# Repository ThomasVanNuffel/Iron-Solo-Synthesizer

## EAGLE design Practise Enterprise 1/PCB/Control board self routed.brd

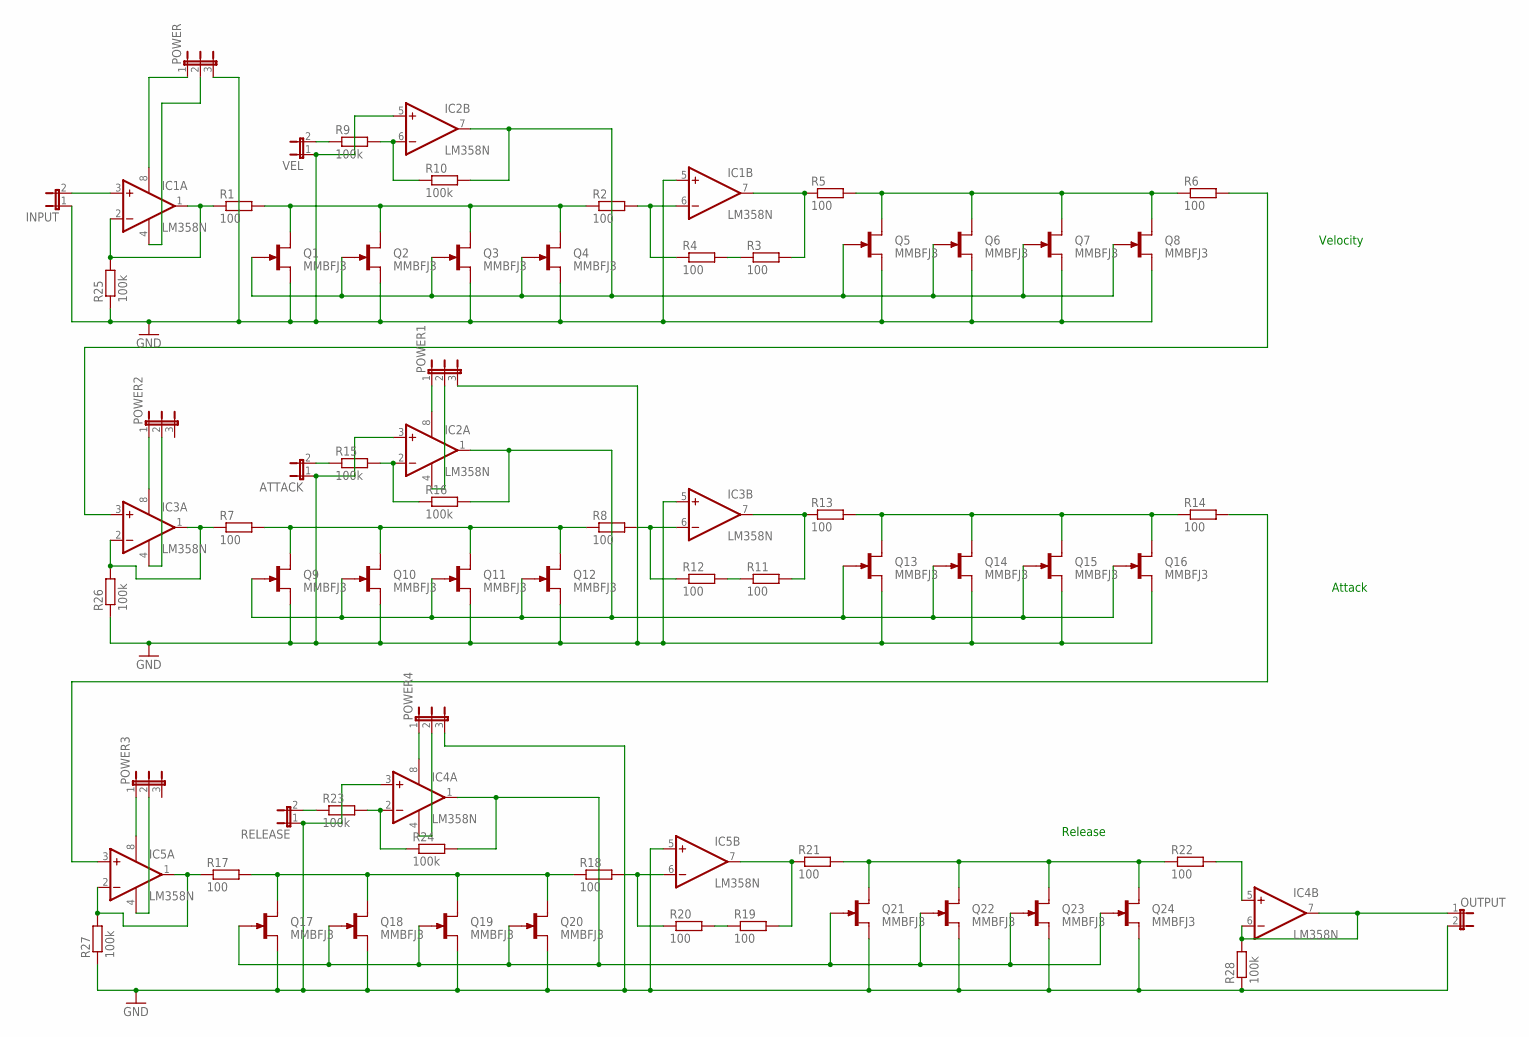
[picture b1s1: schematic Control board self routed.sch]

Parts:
ATTACK: JP1E; JP1
IC1, IC2, IC3, IC4, IC5: LM358N; DIL08
INPUT: JP1E; JP1
OUTPUT: JP1E; JP1
POWER, POWER1, POWER2, POWER3, POWER4: JP2E; JP2
Q1, Q2, Q3, Q4, Q5, Q6, Q7, Q8, Q9, Q10, Q11, Q12, Q13, Q14, Q15, Q16, Q17, Q18, Q19, Q20, Q21, Q22, Q23, Q24: MMBFJ3; SOT23
R1, R2, R3, R4, R5, R6, R7, R8, R11, R12, R13, R14, R17, R18, R19, R20, R21, R22: 100; 0204/7
R9, R10, R15, R16, R23, R24, R25, R26, R27, R28: 100k; 0204/7
RELEASE: JP1E; JP1
VEL: JP1E; JP1

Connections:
22: Q13.1 (D), Q14.1 (D), Q15.1 (D), Q16.1 (D), R13.2, R14.1
CONTROL: IC2.7 (OUT), Q1.3 (G), Q2.3 (G), Q3.3 (G), Q4.3 (G), Q5.3 (G), Q6.3 (G), Q7.3 (G), Q8.3 (G), R10.2
CONTROL1: IC2.1 (OUT), Q9.3 (G), Q10.3 (G), Q11.3 (G), Q12.3 (G), Q13.3 (G), Q14.3 (G), Q15.3 (G), Q16.3 (G), R16.2
CONTROL2: IC4.1 (OUT), Q17.3 (G), Q18.3 (G), Q19.3 (G), Q20.3 (G), Q21.3 (G), Q22.3 (G), Q23.3 (G), Q24.3 (G), R24.2
GND: ATTACK.1, IC1.5 (+IN), IC2.3 (+IN), IC2.5 (+IN), IC3.5 (+IN), IC4.3 (+IN), IC5.5 (+IN), INPUT.1, OUTPUT.2, POWER.3, POWER1.3, POWER4.3, Q1.2 (S), Q2.2 (S), Q3.2 (S), Q4.2 (S), Q5.2 (S), Q6.2 (S), Q7.2 (S), Q8.2 (S), Q9.2 (S), Q10.2 (S), Q11.2 (S), Q12.2 (S), Q13.2 (S), Q14.2 (S), Q15.2 (S), Q16.2 (S), Q17.2 (S), Q18.2 (S), Q19.2 (S), Q20.2 (S), Q21.2 (S), Q22.2 (S), Q23.2 (S), Q24.2 (S), R25.1, R26.1, R27.1, R28.1, RELEASE.1, VEL.1
unnamed: IC4.8 (V+), POWER4.1
unnamed: IC1.8 (V+), POWER.1
unnamed: IC1.6 (-IN), R2.2, R4.1
unnamed: IC1.1 (OUT), IC1.2 (-IN), R1.1, R25.2
unnamed: R3.1, R4.2
unnamed: IC4.4 (V-), POWER4.2
unnamed: IC1.7 (OUT), R3.2, R5.1
unnamed: R9.1, VEL.2
unnamed: IC5.1 (OUT), IC5.2 (-IN), R17.1, R27.2
unnamed: IC1.3 (+IN), INPUT.2
unnamed: IC5.8 (V+), POWER3.1
unnamed: IC2.6 (-IN), R9.2, R10.1
unnamed: IC4.6 (-IN), IC4.7 (OUT), OUTPUT.1, R28.2
unnamed: IC5.4 (V-), POWER3.2
unnamed: IC3.6 (-IN), R8.2, R12.1
unnamed: R11.1, R12.2
unnamed: IC3.7 (OUT), R11.2, R13.1
unnamed: IC3.8 (V+), POWER2.1
unnamed: IC4.5 (+IN), R22.2
unnamed: ATTACK.2, R15.1
unnamed: IC2.2 (-IN), R15.2, R16.1
unnamed: IC3.4 (V-), POWER2.2
unnamed: IC2.8 (V+), POWER1.1
unnamed: IC1.4 (V-), POWER.2
unnamed: IC2.4 (V-), POWER1.2
unnamed: IC5.6 (-IN), R18.2, R20.1
unnamed: R19.1, R20.2
unnamed: IC5.7 (OUT), R19.2, R21.1
unnamed: IC3.3 (+IN), R6.2
unnamed: R23.1, RELEASE.2
unnamed: IC4.2 (-IN), R23.2, R24.1
unnamed: IC5.3 (+IN), R14.2
unnamed: IC3.1 (OUT), IC3.2 (-IN), R7.1, R26.2
NET11: Q1.1 (D), Q2.1 (D), Q3.1 (D), Q4.1 (D), R1.2, R2.1
NET12: Q5.1 (D), Q6.1 (D), Q7.1 (D), Q8.1 (D), R5.2, R6.1
NET21: Q9.1 (D), Q10.1 (D), Q11.1 (D), Q12.1 (D), R7.2, R8.1
NET31: Q17.1 (D), Q18.1 (D), Q19.1 (D), Q20.1 (D), R17.2, R18.1
NET32: Q21.1 (D), Q22.1 (D), Q23.1 (D), Q24.1 (D), R21.2, R22.1

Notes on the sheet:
Velocity
Attack
Release

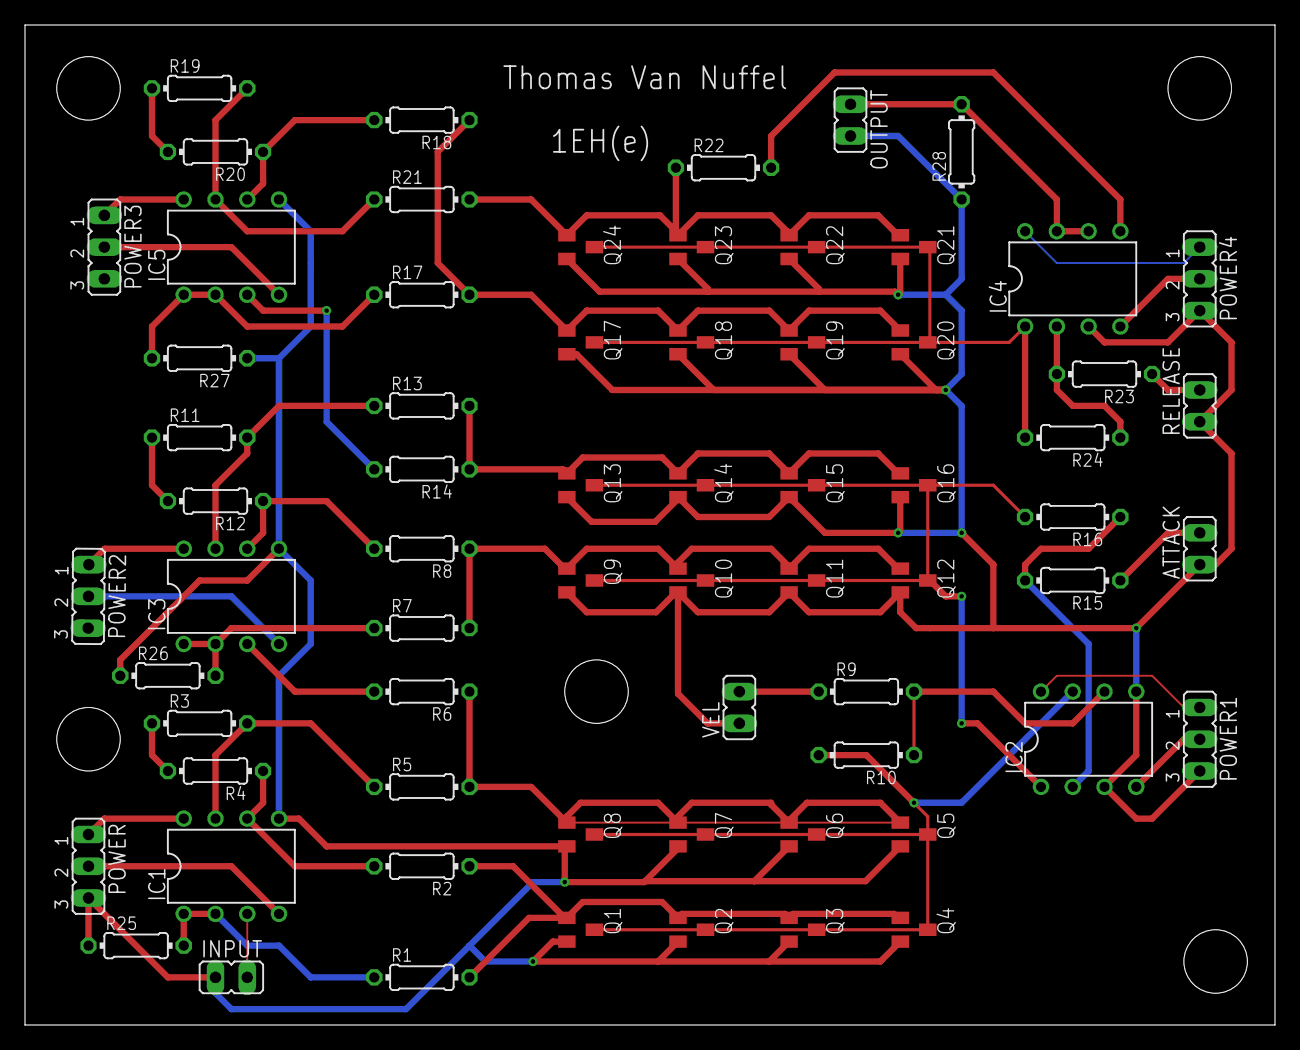
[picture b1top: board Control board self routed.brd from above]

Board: 2 copper layers, 100.0 x 80.0 mm, 67 parts (0 on the bottom side), 43 nets.

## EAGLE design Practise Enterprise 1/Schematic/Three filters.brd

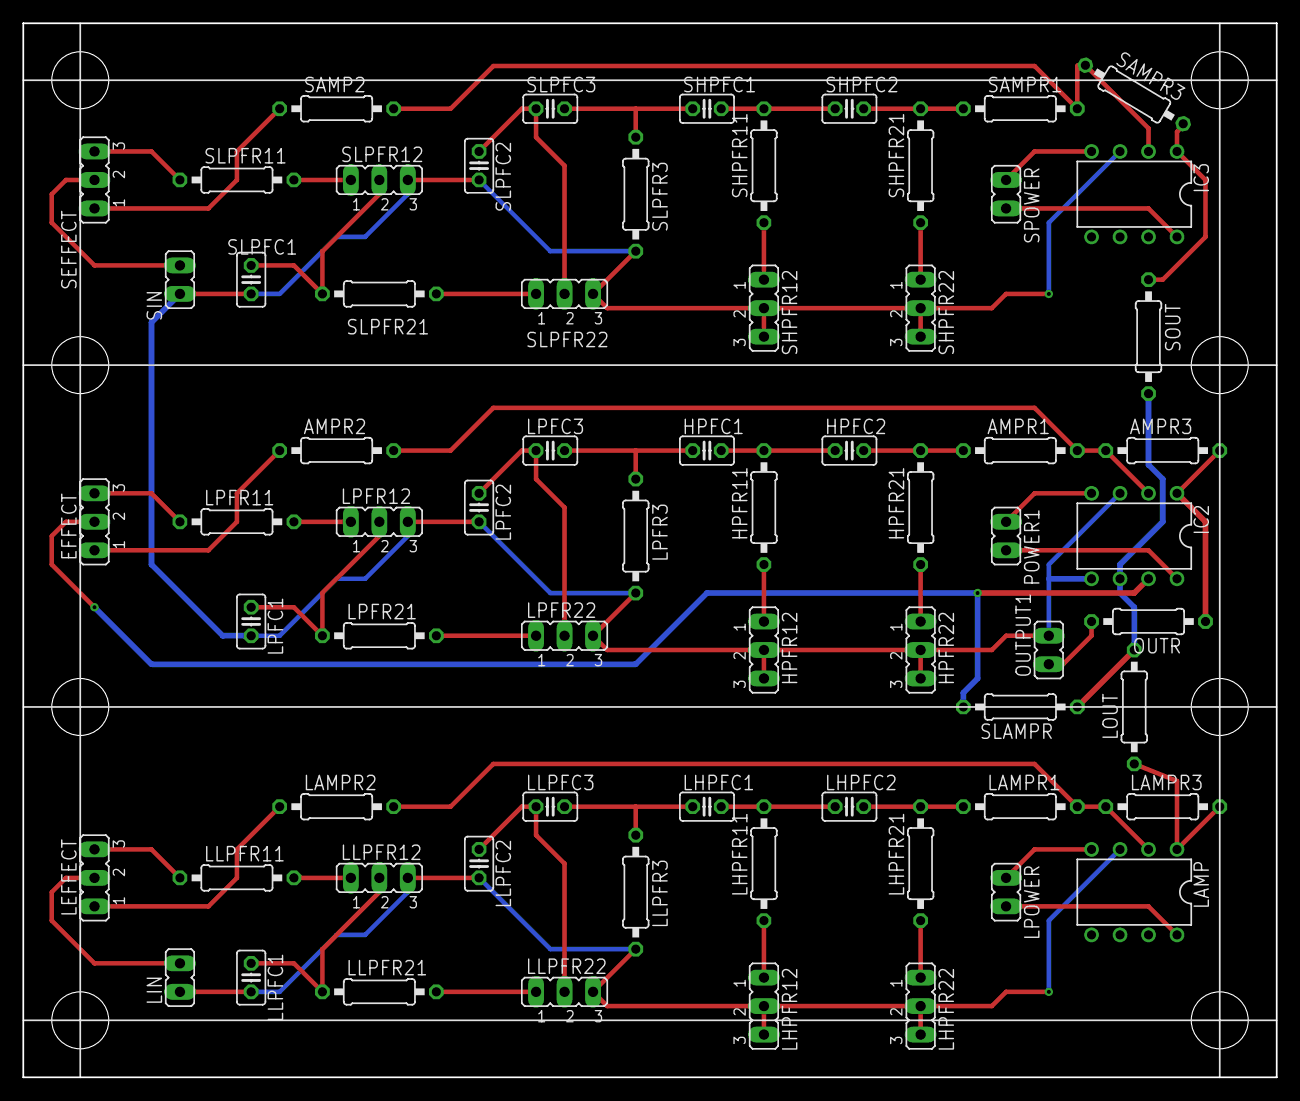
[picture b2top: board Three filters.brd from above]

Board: 2 copper layers, 111.8 x 94.0 mm, 67 parts (0 on the bottom side), 52 nets.

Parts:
AMPR1, AMPR2: 10k; 0207/10
AMPR3: 20k; 0207/10
EFFECT: 220k log; JP2
HPFC1, HPFC2: 47n; C025-025X050
HPFR11, HPFR21: 150; 0207/10
HPFR12, HPFR22: 220k log; JP2
IC2, IC3: LM358N; DIL08
LAMP: LM358N; DIL08
LAMPR1, LAMPR2: 10k; 0207/10
LAMPR3: 20k; 0207/10
LEFFECT: 220k log; JP2
LHPFC1, LHPFC2: 47n; C025-025X050
LHPFR11, LHPFR21: 150; 0207/10
LHPFR12, LHPFR22: 220k log; JP2
LIN: JP1
LLPFC1, LLPFC2: 47n; C025-025X050
LLPFC3: 100n; C025-025X050
LLPFR3: 100k; 0207/10
LLPFR11, LLPFR21: 150; 0207/10
LLPFR12, LLPFR22: 220k log; JP2
LOUT: 10k; 0207/10
LPFC1, LPFC2: 47n; C025-025X050
LPFC3: 100n; C025-025X050
LPFR3: 100k; 0207/10
LPFR11, LPFR21: 150; 0207/10
LPFR12, LPFR22: 220k log; JP2
LPOWER: JP1
OUTPUT1: JP1
OUTR: 100; 0207/10
POWER1: JP1
SAMP2: 10k; 0207/10
SAMPR1: 10k; 0207/10
SAMPR3: 20k; 0207/10
SEFFECT: 220k log; JP2
SHPFC1, SHPFC2: 47n; C025-025X050
SHPFR11, SHPFR21: 150; 0207/10
SHPFR12, SHPFR22: 220k log; JP2
SIN: JP1
SLAMPR: 10k; 0207/10
SLPFC1, SLPFC2: 47n; C025-025X050
SLPFC3: 100n; C025-025X050
SLPFR3: 100k; 0207/10
SLPFR11, SLPFR21: 150; 0207/10
SLPFR12, SLPFR22: 220k log; JP2
SOUT: 10k; 0207/10
SPOWER: JP1

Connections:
unnamed: LLPFR11.2, LLPFR12.1
unnamed: LLPFC1.1, LLPFR12.2, LLPFR21.1
unnamed: LLPFC2.1, LLPFC3.1, LLPFR22.2
unnamed: LAMP.3, LHPFR12.2, LHPFR12.3, LHPFR22.2, LHPFR22.3, LIN.1, LLPFC1.2, LLPFC2.2, LLPFR3.2, LLPFR12.3, LLPFR22.3
unnamed: LEFFECT.3, LLPFR11.1
unnamed: LHPFC1.2, LHPFC2.1, LHPFR11.2
unnamed: LPFR11.2, LPFR12.1
unnamed: LAMP.1, LAMPR3.2, LOUT.1
unnamed: LAMP.8, LPOWER.2
unnamed: LAMP.4, LPOWER.1
unnamed: LAMPR2.1, LEFFECT.1
unnamed: LLPFR21.2, LLPFR22.1
unnamed: LHPFR21.1, LHPFR22.1
unnamed: LAMPR1.1, LHPFC2.2, LHPFR21.2
unnamed: LHPFR11.1, LHPFR12.1
unnamed: LPFC1.1, LPFR12.2, LPFR21.1
unnamed: LPFC2.1, LPFC3.1, LPFR22.2
unnamed: LHPFC1.1, LLPFC3.2, LLPFR3.1
unnamed: LEFFECT.2, LIN.2
unnamed: LAMP.2, LAMPR1.2, LAMPR2.2, LAMPR3.1
unnamed: HPFC1.2, HPFC2.1, HPFR11.2
unnamed: IC2.8, POWER1.2
unnamed: IC2.4, POWER1.1
unnamed: OUTPUT1.1, OUTR.2
unnamed: LPFR21.2, LPFR22.1
unnamed: AMPR1.1, HPFC2.2, HPFR21.2
unnamed: HPFR21.1, HPFR22.1
unnamed: HPFR11.1, HPFR12.1
unnamed: HPFC1.1, LPFC3.2, LPFR3.1
unnamed: EFFECT.2, IC2.7, SLAMPR.2
unnamed: AMPR1.2, AMPR2.2, AMPR3.1, IC2.2
unnamed: AMPR2.1, EFFECT.1
unnamed: EFFECT.3, LPFR11.1
unnamed: SLPFR11.2, SLPFR12.1
unnamed: SLPFC1.1, SLPFR12.2, SLPFR21.1
unnamed: SLPFC2.1, SLPFC3.1, SLPFR22.2
unnamed: HPFR12.2, HPFR12.3, HPFR22.2, HPFR22.3, IC2.3, IC2.5, IC3.3, LPFC1.2, LPFC2.2, LPFR3.2, LPFR12.3, LPFR22.3, OUTPUT1.2, SHPFR12.2, SHPFR12.3, SHPFR22.2, SHPFR22.3, SIN.1, SLPFC1.2, SLPFC2.2, SLPFR3.2, SLPFR12.3, SLPFR22.3
unnamed: SHPFC1.2, SHPFC2.1, SHPFR11.2
unnamed: IC3.8, SPOWER.2
unnamed: IC3.4, SPOWER.1
unnamed: IC3.1, SAMPR3.2, SOUT.1
unnamed: SLPFR21.2, SLPFR22.1
unnamed: SAMPR1.1, SHPFC2.2, SHPFR21.2
unnamed: SHPFR21.1, SHPFR22.1
unnamed: SHPFR11.1, SHPFR12.1
unnamed: SHPFC1.1, SLPFC3.2, SLPFR3.1
unnamed: SEFFECT.2, SIN.2
unnamed: IC3.2, SAMP2.2, SAMPR1.2, SAMPR3.1
unnamed: SAMP2.1, SEFFECT.1
unnamed: SEFFECT.3, SLPFR11.1
S$1: IC2.6, LOUT.2, SLAMPR.1, SOUT.2
S$2: AMPR3.2, IC2.1, OUTR.1
